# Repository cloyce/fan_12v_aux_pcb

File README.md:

# Power distribution and tap board

I have a 1U server case that holds 6 40mm x 40mm fans.

The motherboard in that server case has headers for two case fans.

I have 6 40mm x 40mm fans salvaged from dead power supplies.  The fans "feature" a JST SHR04V-S connector attached to short leads.  I could (and have) cut them off, soldered on longer leads, and put larger crimp connectors on the end, but that is *super* tedious.  I don't want to have to do that whenever a fan fails, and I don't want to have to do that ahead of time either.

So to kill two birds with one stone, I've designed this board which will take power from one of the motherboard headers and distribute it to three unmodified fans.  The tach signal is taken from FAN2; the PWM signal is distributed to all three fans.

I have another requirement, and that is to power a RouterBoard I have inside the case.  When the system is off I run it off a DC-DC boost converter connected to +5V housekeeping, but that's close to the current limit of the housekeeping line, and the DC-DC converter is cheap and I don't want to stress it, so I want to source current from elsewhere while the system is on.

And that's where the tap comes in.

If for some reason you're in the same situation as me with respect to the fans, you can just populate FAN_12V_IN and FAN1 - FAN3 and be in business.  If you want to do the power tap thing, you need to populate the 12V_AUX_OUT header and the half-bridge diode.  If you want to possibly feed in from another source (like the other fan board), you'll need to populate the 12V_AUX_IN header as well.

All of these are designed to take the special 4-pin headers with the offset key, but assuming that there's no keying pin (or that it's in the same place), there's no reason a normally keyed or unkeyed 0.100" header wouldn't work.

Still, here's the BOM I'm using:

|Part #|Qty|Digikey Part|Mouser Part|Description|
|----|----|----|----|----|
|Molex 47053-1000|1-3|WM4330-ND|538-47053-1000|4-pin offset key header|
|SBR1040CT|0-1|SBR1040CTDI-ND|621-SBR1040CT|Dual common-cathode diode array, 40V 5A|
|JST SM04B-SRSS-TB(LF)(SN)|1-3|455-1804-2-ND|N/A|JST SH series 4-pin SMD header|

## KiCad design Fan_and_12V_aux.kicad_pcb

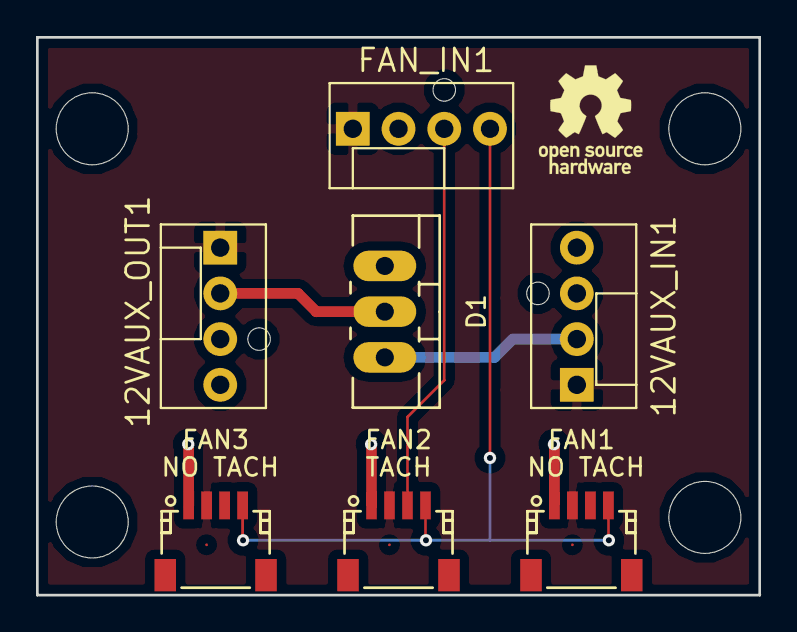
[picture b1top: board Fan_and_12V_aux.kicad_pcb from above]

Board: 2 copper layers, 40.1 x 31.0 mm, 11 parts (0 on the bottom side), 6 nets.

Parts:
12VAUX_IN1, 12VAUX_OUT1: FAN-4PIN-PWM; cds-FAN_PWM
D1: D_x2_KCom_AKA; TO-220_Neutral123_Vertical_LargePads
FAN1, FAN2, FAN3: FAN-SM04B; JST_SH_SM04B-SRSS-TB_04x1.00mm_Angled
FAN_IN1: FAN-4PIN-PWM; cds-FAN_PWM
MH1, MH2, MH3, MH4: MountingHole_4mm

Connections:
+12V: D1.1, FAN1.1, FAN2.1, FAN3.1, FAN_IN1.2
GND: 12VAUX_IN1.1, 12VAUX_OUT1.1, FAN1.2, FAN2.2, FAN3.2, FAN_IN1.1
unnamed: 12VAUX_IN1.2, D1.3
unnamed: 12VAUX_OUT1.2, D1.2
unnamed: FAN1.4, FAN2.4, FAN3.4, FAN_IN1.4
unnamed: FAN2.3, FAN_IN1.3

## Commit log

2017-04-01 rev 1
2017-04-06 added README
2017-04-06 Create LICENSE
